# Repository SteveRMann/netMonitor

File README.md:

# net_monitor
Sketch to monitor the status of my router, internet connection and local servers.
----
My Smart Home has grown into a Frankenstein monster.

I started with Node-Red and Mosquitto MQTT broker on a single Raspberry Pi3.  At some point I wanted to add some Z-Wave
devices and someone on the Node-Red forums told me that my best route was to install Home Assistant and an Aeotec Z-Stick,
then I could control the Z-Wave devices from Node-red.  I didn't want to risk messing up my currently running Pi with
Node-red and Mosquitto, so I installed Home Assistant on a second Raspberry Pi.  I discovered that I like Home Assistant
and instead of growing my system on Node-Red, as originally planned, I spent the next months adding more devices to Home Assistant.

So now I had two Raspberry Pis running my smart home.  Then came the Tradfri lights, so add the Tradfri Gateway to the mix.
Next, I added some IP cameras.

So when my wife says that "Alexa isn't listening to me!", I have a number of places to look for the problem.
(Since I am always doing something to my stuff, I am always breaking something).

My troubleshooting process involves pinging all the likely suspects to make sure they are all online.  I wanted a faster and
easier way to determine where to start looking for a problem.  Thus was born my Net Monitor Applpiance project.

The Net Monitor Appliance just pings the IP address of the critical devices on my network, and if a good ping is found,
lights a green LED.  If a ping is not responsive, a red LED lights.  The loop repeats every 30-seconds.  So, if I look up
and see a "green board", then I know not to take the time to ping up to 10 devices.

I chose to make the Net Monitor on the NodeMCU platform because it has WiFi and works from any 5V micro-USB wall wart.
I could have easily included an LCD display, but I just wanted to have something to determine at a glance if I have a net problem.

## To Do
Check out a different esp8266ping.h library
https://github.com/dancol90/ESP8266Ping/blob/master/examples/SimplePing/SimplePing.ino

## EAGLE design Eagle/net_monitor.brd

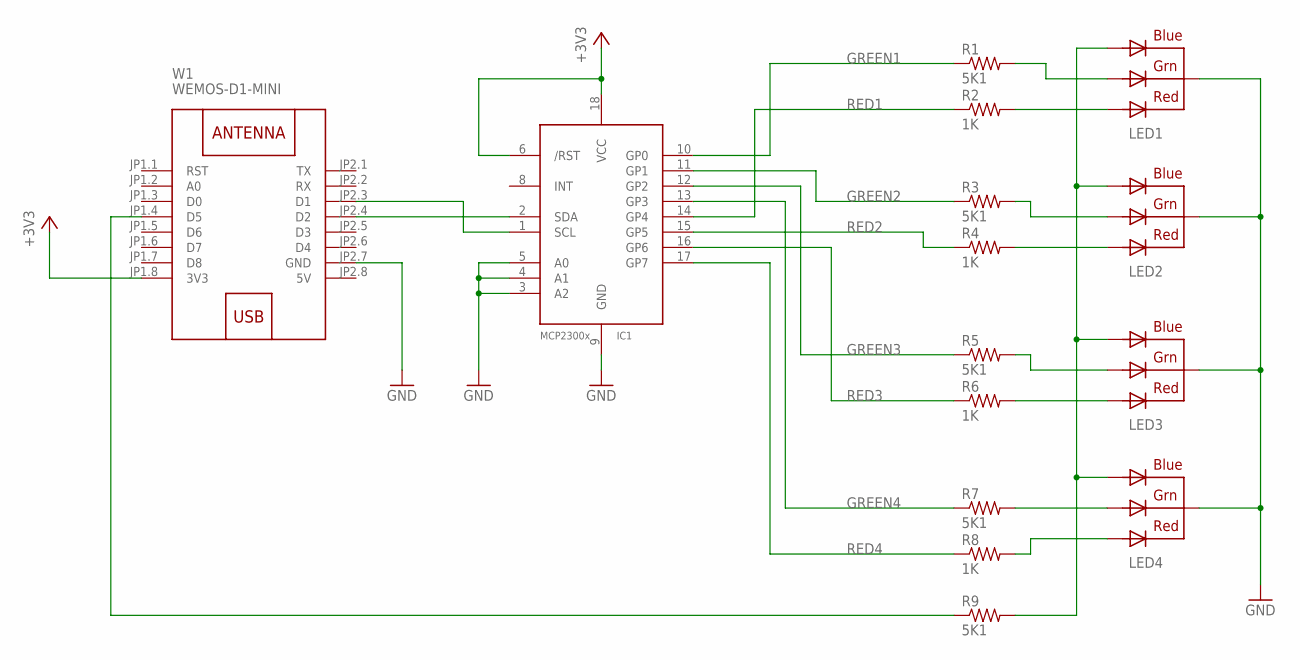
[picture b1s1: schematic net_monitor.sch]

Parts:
IC1: MCP23008/P; DIL18
LED1, LED2, LED3, LED4: RGBLED_CC; LED5MMRGB
R1, R3, R5, R7, R9: 5K1; 0207/10; MPN CRCW12065K10FKEA
R2, R4, R6, R8: 1K; 0207/10
W1: WEMOS-D1-MINI

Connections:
5V: W1.JP2.8 (5V)
+3V3: IC1.6 (/RST), IC1.18 (VCC), W1.JP1.8 (3V3)
GND: IC1.3 (A2), IC1.4 (A1), IC1.5 (A0), IC1.9 (GND), LED1.2 (CATHODE), LED2.2 (CATHODE), LED3.2 (CATHODE), LED4.2 (CATHODE), W1.JP2.7 (GND)
GREEN1: IC1.10 (GP0), R1.1
GREEN2: IC1.11 (GP1), R3.1
GREEN3: IC1.12 (GP2), R5.1
GREEN4: IC1.13 (GP3), R7.1
unnamed: LED4.3 (GREEN), R7.2
unnamed: LED1.3 (GREEN), R1.2
unnamed: LED1.4 (BLUE), LED2.4 (BLUE), LED3.4 (BLUE), LED4.4 (BLUE), R9.2
unnamed: LED1.1 (RED), R2.2
unnamed: LED3.3 (GREEN), R5.2
unnamed: LED3.1 (RED), R6.2
unnamed: LED2.3 (GREEN), R3.2
unnamed: LED2.1 (RED), R4.2
unnamed: IC1.1 (SCL), W1.JP2.3 (D1)
unnamed: LED4.1 (RED), R8.2
unnamed: R9.1, W1.JP1.4 (D5)
unnamed: IC1.2 (SDA), W1.JP2.4 (D2)
RED1: IC1.14 (GP4), R2.1
RED2: IC1.15 (GP5), R4.1
RED3: IC1.16 (GP6), R6.1
RED4: IC1.17 (GP7), R8.1

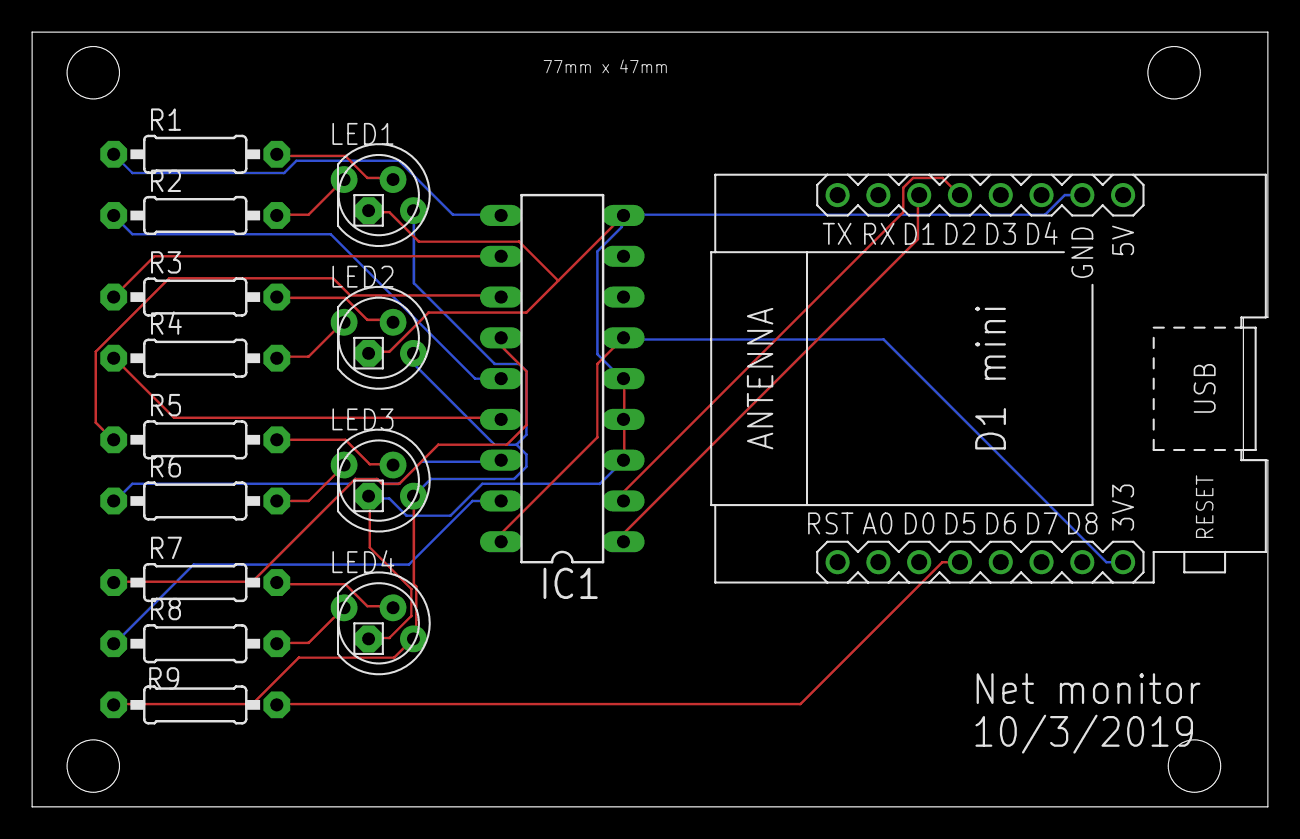
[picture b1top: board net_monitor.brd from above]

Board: 2 copper layers, 77.0 x 48.2 mm, 15 parts (0 on the bottom side), 22 nets.

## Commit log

2019-09-05 Version 3.0 9/4/2019 Working with three-color LEDs
2019-09-11 Cleanup of the Kaywinnet.h file.
2019-10-02 Removed local router from the ping list, added plex server. (If the router is offline, no other pings would work anyway).
    Added Eagle folder to the git
2019-10-03 Added stuff to gitignore
2020-02-17 Version 3.0, 2/17/2020- Added OTA
2020-04-23 Changed one IP
2020-05-09 Clean up some comments
2020-08-25 Added MQQT
    Added MQQT to publish the IP of the failed pings. This is used to make a log file in Node red.
2021-03-11 Version 5.1 3/10/2021 Publish the failing IP.
2021-03-12 Added four new and removed two problematic external IPs
    Version 5.2 3/12/2021
    Added four new and removed two problematic external IPs
2021-03-12 Fixed the comments in netMonitor.ino
2021-03-16 Check for MQTT connection with each ping. Log all fails.
    Version 5.3 3/16/2021
    Check for MQTT connection with each ping. Log all fails.
2021-03-25 Delete Serial.ino
    Renamed to 'serial.ino'
2021-03-25 Version 6, Made the hostName dynamic
    Version 6.0 3/24/21
    Made the hostName dynamic, prefix+last 3 bytes of the MAC
    Use hostName for MQTT connect.
2021-09-11 Fixed a comma error in iplist.h
2021-09-11 Really fixed the comma error in iplist.h
2021-09-11 Removed external IP addresses that fail the most.
2022-03-06 Changed wifi.ino to wIfiMulti.ino
2022-03-12 Update IP list
2022-10-02 Update the WiFi credentials (spelling)
2022-11-06 Removed outlook.com from external IP list
2022-12-17 Added a test for wifi connected.
2022-12-18 Removed MQTT
    Removing MQTT has increased the reliability of the monitor to recover from WiFi hiccups.
2023-02-21 Remove more MQTT lines
2023-05-22 Added a notch in the PCB for the USB connector
2023-11-08 Removed WiFiMulti
2023-11-27 Forked from netMonitor
    netmonitor2: Removed WiFimulti, ticker, mqtt
2024-02-12 Leaner version
2024-04-18 Update hosts.h
    New IP for Zeus.
2025-05-11 Moved schematic to images

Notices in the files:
parts and their libraries:
diy-modules: Released under the Creative Commons Attribution 4.0 International License: http://creativecommons.org/licenses/by/4.0
